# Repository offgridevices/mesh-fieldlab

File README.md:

# mesh-fieldlab

Open measurement and packet-logging tooling for LoRa mesh field tests.

**Status:** early. Structure and scope are being set up; implementation is in progress.

## Why this exists

A Meshtastic node paired with a phone shows you signal strength *live*. That is useful for a smoke test and useless for a measurement. It does not write every packet to a file, so there is no way to turn "I saw a few bars on my phone out there" into a dataset you can analyse, plot, or hand to somebody else.

`mesh-fieldlab` is the logging layer that closes that gap. It tethers to LoRa mesh nodes in the field, records what actually arrives, and writes it to disk in a stable format so that outdoor tests produce evidence instead of impressions.

## Scope

This repository is **measurement and analysis only**. Concretely, that means:

**In scope**
- Connecting to Meshtastic nodes over USB/serial (and BLE where practical)
- Recording every received packet: timestamp, source, destination, RSSI, SNR, hop count, port/type
- Stable CSV schemas that stay readable years from now
- Per-node test metadata: GPS position, antenna, height above ground, firmware and radio settings
- Derived measures such as packet delivery ratio and per-link statistics
- Analysis notebooks and plots over collected runs
- Hardware setup, wiring, and power notes for the logging rig
- Clock synchronisation and calibration procedures

**Out of scope**
- Anything unrelated to capturing or analysing measurements
- Vendored third-party source (see below)
- Credentials, API keys, or private configuration
- Raw logs containing precise coordinates of private property

## Intended hardware

- **Nodes:** RAK WisBlock / RAK4631 running Meshtastic, US915 region. Every node in a run is pinned to the **same** firmware version — currently `v2.7.26`, the `rak4631` build — because mixed versions produce measurements that look comparable and are not
- **Logger:** Seeed XIAO ESP32-C6 wired to the node's UART header, writing to a microSD card. It speaks the Meshtastic client protocol over serial — the same one a phone uses — so the node needs no modified firmware.
- **Status display:** a small OLED runs a self-test at power-up — card writable, radio answering, region and preset correct, position and clock set, which neighbours are audible — then blanks. A button wakes it for ten seconds. This is what replaces having a phone at each node.
- **Power:** a single LiPo on the node's battery connector feeds both boards; there is no second supply and no 5 V rail. A switch in the battery lead turns the whole node on and off; each power-up starts a new log file, so cycling a node is safe.
- Anything else that speaks the Meshtastic serial protocol should work.

See [docs/packet-logger-design.md](docs/packet-logger-design.md) for the wiring, file format, and validation procedure.

## Dependencies and licensing

This project depends on the official [Meshtastic Python library](https://github.com/meshtastic/Meshtastic-python) and, for the logger firmware, on [Meshtastic-arduino](https://github.com/meshtastic/Meshtastic-arduino). Both are licensed **GPL-3.0**, so **this repository is also licensed GPL-3.0**. That is a deliberate choice rather than a default: it keeps the licensing honest and unambiguous.

Expected dependency set:

| Dependency | Purpose | License |
|---|---|---|
| `meshtastic` | Node communication (Python tooling) | GPL-3.0 |
| `Meshtastic-arduino` | Node communication (logger firmware) | GPL-3.0 |
| `U8g2` | Status display (logger firmware) | BSD-2-Clause |
| `pyserial` | Serial transport | BSD-3-Clause |
| `pandas` | Log analysis | BSD-3-Clause |
| `matplotlib` | Plots | PSF-based |
| `pytest` | Tests (development only) | MIT |

If you add a dependency, record its license in this table in the same commit.

The log validator in `tools/` deliberately has **no runtime dependencies at all**: it needs to run on whatever laptop is in the field, against a card that was just pulled out of a node, without installing anything first.

### Our fork of Meshtastic-arduino

The firmware builds against [`offgridevices/Meshtastic-arduino`](https://github.com/offgridevices/Meshtastic-arduino), a fork of the upstream library, pinned to an exact commit.

The fork exists for one reason: upstream decodes each packet's RSSI and SNR and then discards them — none of its three callbacks pass those fields to the caller, and no setting changes that. Since RSSI and SNR are the entire measurement, the fork adds one additional callback carrying the full packet metadata, along with an example sketch and a host-side test suite that runs without a radio. Existing callbacks and return values are untouched. The change will be offered upstream once it has been validated in the field.

The fork remains GPL-3.0, and its commit history is the record of what was modified.

## Third-party source is never vendored here

Dependencies are installed from package managers, or referenced by URL and pinned commit. Source copies of external projects are **not** committed to this repository, and are not kept inside this working tree at all — local clones used for reading or reference live outside it, and `.gitignore` additionally blocks the usual paths (`reference/`, `vendor/`, `third_party/`, `external/`) so that an accidental copy cannot be staged.

This matters for a practical reason: license obligations travel with code. Keeping other projects' source physically outside this tree means the provenance of everything committed here is unambiguous, both for this repository and for any other project developed alongside it.

**When a dependency must be modified**, it is forked into its own repository and referenced here by URL and exact commit — never copied in and edited in place. What this repository commits is a reference, so provenance stays trivially answerable, and the fork's own commit history serves as the record of modification that GPL-3.0 requires. Record any such fork in the dependency table above, with its license and the reason it exists.

**If you are contributing:** do not paste code in from another project. Import it as a dependency, fork it and pin it, or write it yourself.

## Data handling

Collected logs are the point of this repository, but not all of them belong in it. Before committing a run:

- Confirm the test location is not private property whose coordinates you would rather not publish
- Strip or round coordinates where precision is not needed for the analysis
- Keep raw captures and processed results clearly separated

## License

GPL-3.0. See [LICENSE](LICENSE).

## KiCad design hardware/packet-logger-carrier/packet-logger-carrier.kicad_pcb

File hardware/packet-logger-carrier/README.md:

# Packet Logger Carrier Board — v1

A single 2-layer PCB that replaces the hand-wired 7 × 9 cm protoboard node.
Drop in the **RAK19003**, the **XIAO ESP32-C6** and the **microSD breakout**,
add a button and a power switch, and every connection in the build record is
made in copper instead of wire.

**Board: 86 × 58 mm, 2 layers, 1.6 mm FR4.**
65 solder points. 98 track segments, 8 vias, full ground plane underneath.

Opens in **KiCad 10** — the board file is saved in KiCad 10's own native
format and KiCad's DRC reports **0 errors, 0 warnings, 0 unconnected**.

---

## Brand colours — how to order it

**Colour is not in the Gerber files.** Soldermask and silkscreen colour are
options you pick in the fab's order form; the artwork is colour-blind. So
"on-brand" here means two things: choosing the right options, and designing
the artwork to suit them. Both are done.

| OffGrid token | On the board | Order setting |
|---|---|---|
| **Pitch** `#1B1813` | Soldermask | **Matte black** (JLCPCB "Matt Black", PCBWay "Matte Black") |
| **Bone** `#F1ECE0` | Silkscreen | **White** |
| **Ember** `#FF6A00` | The Beacon Ring, in bare metal | **ENIG** surface finish |

### The lockup

The mark and wordmark are placed at the ratios in
`handoff/logo/svg/offgrid-wordmark-horizontal.svg` — mark at `translate(20 12)`,
text anchored at `x=240 y=125`, size 92, letter-spacing −3 — scaled as one unit
so the spacing is the brand's, not an approximation. The wordmark is set in
**real Archivo weight 900 outlines**, pulled from the variable font and emitted
as filled polygons, rather than a stand-in stroke font. `src/verify_wordmark.py`
re-renders the same text through FreeType and compares shapes as a build gate.

Mark height 5.4 mm, lockup 21 mm wide, cap height 2.3 mm.

One deliberate departure: the brand SVG's own text baseline (`y=125`) leaves the
wordmark sitting about **12% of the mark height too high**, which reads as
misaligned at this size. The wordmark is dropped so its ink centre lands on the
mark's area centroid (ring + node) — the optical centre. Worth correcting in the
source asset too.

No board house offers orange soldermask, so Ember is expressed the only way a
PCB can: as **exposed copper**. The Beacon Ring is drawn on the copper layer
with a matching opening in the soldermask, so it comes out as bare gold metal
against the black — the same warm accent, in the only material the process
allows. The wordmark beside it stays white silkscreen, which keeps to the
brand's **one accent per surface** rule: the ring is the accent, everything
else is Bone on Pitch.

ENIG rather than HASL matters here — HASL would coat the mark in solder and it
would come out silver. ENIG also has a longer shelf life and a flatter finish.
It costs a little more than the default; it is the difference between a gold
mark and a grey one.

The board outline is a plain rectangle with square corners, per the brand's
right-angles-only geometry rule.

**Full order settings:** 2 layers · 1.6 mm · **Matte black** mask · **White**
silkscreen · **ENIG** finish · 86 × 58 mm · qty 5.

One practical note: matte black shows fingerprints and dust more than green,
and cosmetic consistency between batches is slightly looser. Nothing about it
affects how the board works — our traces are 0.25 mm against a 0.127 mm
process minimum, so there is a wide margin.

---

## ⚠ Read this before you order

**The RAK19003's two headers are NOT a whole number of protoboard holes apart.**

Measured from RAK's own mechanical drawings (both the Rev B dimensioned drawing
and the Rev E drawing, which agree to 0.03 mm):

| | |
|---|---|
| Pitch inside each 4-pin group | 2.54 mm |
| **Gap, J6 pin 4 (SDA) → J7 pin 1 (BOOT)** | **9.41 mm** |
| Which is | 3.70 × 2.54 — *not* 4 holes (10.16 mm) |
| Total span, pin 1 to pin 8 | 24.65 mm |

That is why the RAK was a squeeze on the protoboard: putting J6 in columns
A–D and J7 in H–K forces the pins about 0.75 mm out of place.

**How this board handles it:** J6's four pads are round holes on an exact
2.54 mm pitch. J7's four pads are **oval slots (1.0 × 2.0 mm)** centred at a
9.79 mm gap. That accepts anything from **9.24 mm to 10.34 mm**, so the board
solders up whether the true gap is the datasheet's 9.41 or a full 10.16.

**Still do this before ordering:** put a caliper across your actual RAK from
the centre of the SDA pin to the centre of the BOOT pin. Anything in
9.2 – 10.3 mm is covered.

---

## How each module sits

Hold the board with the text the right way up. Then:

**RAK19003** — pins along the bottom, body reaching up. Its USB-C, battery,
solar and reset are all on the **far (top) edge**, so they stay reachable.
Left to right the pins read:

```
J6:  VDD   GND   SCL   SDA        [ 9.41 mm gap ]        J7:  BOOT  GND  TX0  RX0
```

Confirmed two independent ways: it is what you read off your own board, and it
is what RAK's Figure 3 shows once you rotate the board 90° to match how you
have it mounted. The Rev E silkscreen says **TX0 / RX0** (the older datasheet
table calls the same pins TX1 / RX1 — same physical pins).

**XIAO ESP32-C6** — **USB-C points east**, out to the right-hand edge, so you
can plug in to reprogram it without taking anything apart. Reading the bottom
row from the USB end back: 5V, GND, 3V3, D10, D9, D8, D7 — the standard XIAO
order.

**microSD** — pins along the **top** of the module, body hanging **down toward
the bottom edge of the board**, so the card slot ends up at the edge and you
can pull the card without opening the box. Left to right the pins read:

```
3V3   CS   MOSI   CLK   MISO   GND
```

with **3V3 on the square pad** — matching the module you have.

---

## What's on the board

| Ref | What | Pins |
|---|---|---|
| J1 / J2 | RAK19003 J6 and J7 | 4 + 4 |
| J3 | XIAO ESP32-C6, 2×7, rows 15.24 mm apart | 14 |
| J4 | microSD breakout, 1×6 | 6 |
| **J5** | **OLED display — GND, 3V3, SCL, SDA. Nothing else on it.** | **4** |
| J15 | External button, if you want one off-board — BTN, GND | 2 |
| SW1 | User button, 6 mm tact, on the board | 4 |
| SW2 | **SS-12D00 / SS12D00G6 power slide switch, mounts on the board** | 3 |
| J12 / J13 | Battery in — bare wires or JST-PH 2.0, wired in parallel | 2 + 2 |
| J14 | Switched battery out → the RAK's own battery socket | 2 |
| J10 | RAK spare: BOOT, SCL, SDA, GND | 4 |
| J11 | ESP spare: 5V, D1, D2, GND | 4 |
| JP1 | 3V3 link — **fit a shunt** (see below) | 2 |
| C1–C4 | Decoupling, all optional, all 2.54 mm lead pitch | 8 |

### The power switch

**SW2 takes your SS12D00G6 directly** — three pins on 2.54 mm, which is
exactly what that switch has, so it drops in and solders. The body outline on
the silkscreen is the 8.0 × 4.0 mm footprint of the switch. The **centre pin
is the input** (battery +); the switched output leaves on the pin marked OUT.
The third pin is unconnected. If you would rather use a panel switch, wire it
to OUT and IN instead.

### The display

**J5 is the display and only the display** — four pins, GND, 3V3, SCL, SDA,
all together, labelled on the board. The button is a separate 2-pin header
(J15) right next to it, wired in parallel with the button on the board, so you
can use either, both, or neither.

### The 3V3 link (JP1)

The RAK's 3.3 V comes in on JP1's "RAK" pin and leaves on "SYS" to feed the
XIAO, the card and the OLED. Fit a jumper shunt for normal use.

Pull the shunt when you want to program the XIAO over USB with the RAK
powered — it stops the RAK's regulator and the XIAO's regulator fighting over
the same rail. With the shunt out, USB still powers the XIAO, the card and
the screen; only the RAK is separated. If you'd rather never think about it,
bridge the two pads with solder.

---

## Ordering

JLCPCB or PCBWay:

* 2 layers, 1.6 mm, **matte black mask, white silkscreen, ENIG finish** (see Brand colours above)
* **86 × 58 mm** — inside the cheap 100 × 100 mm tier
* Upload `packet-logger-carrier-gerbers.zip` as-is
* Minimum order is 5; you need 4, so you get a spare
* Expect roughly $2–5 for the bare boards; ENIG and the black mask add a
  few dollars. Plus shipping, about 1–2 weeks.

The zip contains top and bottom copper, both soldermasks, top silkscreen,
board outline, and separate plated / non-plated drill files. J7's oval slots
are in the plated drill file as routed slots (G85) — both houses handle these
as standard.

---

## Assembly order

1. **C1–C4 first** if you're fitting them (lowest parts first). They're optional.
2. **JP1**, then the shunt.
3. **SW1** the tact switch, **SW2** the slide switch.
4. **J12/J13** battery in, **J14** battery out.
5. **J5, J10, J11, J15** male headers.
6. **Female headers last**: J1, J2 (RAK), J3 (XIAO), J4 (card).
7. Plug the modules in. Wire a JST-PH pigtail from **J14** to the RAK's own
   battery socket, and a 4-way cable from **J5** to the display.

Every GND pin sits on a thermal relief, so they solder with a normal iron
instead of sinking all the heat into the ground plane.

### Mounting the modules

Every module interface is a plain 2.54 mm through-hole header, so you can
either socket the module on female headers (easy to swap, ~8.5 mm tall) or
solder wires straight into the same holes and mount the module elsewhere.
Both work.

If you solder a module down flat instead of on headers, note that signal
traces do run underneath it. They are covered by soldermask, so this is
fine — just don't scrape it.

---

## What was checked

Two independent sets of checks, plus KiCad's own:

| Check | Result |
|---|---|
| **KiCad 10 DRC** (the real thing, zones filled) | **0 errors, 0 warnings, 0 unconnected** |
| Copper clearance, every pair of objects on a shared layer | **pass** — 0.25 mm minimum |
| Net connectivity, by flood-fill over both layers | **pass** — every pad on every net reachable |
| Netlist vs. the proven protoboard wiring | **pass** — identical, pin for pin |
| Drill-to-drill spacing | **pass** — minimum 0.45 mm |
| Annular ring | **pass** — minimum 0.15 mm |
| Copper and drills inside the board edge | **pass** |
| Ground pour reaches every GND pad through its thermal spokes | **pass** — all 16 |
| Silkscreen collisions (text/text, text/pad, text/line) | **pass** — none |
| **Gerber round-trip**: emitted Gerbers re-read by a separate parser and compared to the model | **pass** — 0.0000 mm² difference on both copper layers |
| **Cross-check vs KiCad's own Gerber export** of the same board | **F.Cu 0.000 mm², Edge.Cuts 0.000 mm², masks 0.06 mm²** |
| Brand accent is on copper + mask, never silkscreen (regression gate) | **pass** — 37 items on each |
| Silkscreen over mounting holes | **pass** — none |
| Every region inspected visually at readable magnification, both sides | **done** |
| Wordmark outlines vs an independent FreeType rendering | **match** — IoU 0.94, aspect within 0.6% |

The strongest of these is the cross-check: KiCad was asked to export its own
Gerbers from the same board, and its top copper and board outline match ours
to **zero measurable difference**, logo included. The bottom copper differs by
about 1% — entirely at the pour's outer edge and around thermal spokes, where
two different pour algorithms are simply allowed to disagree. Both are valid.

`render3d_top.png` and `render3d_bottom.png` are KiCad's own 3D renders using
the board stackup, so they show the finished product in the colours it will be
built in.

`fab_top.png` and `fab_bottom.png` are rendered *from the Gerbers themselves*,
not from the design, and in the brand colours the board will actually be
ordered in - so what you see there is what will be manufactured.

---

## Assumptions worth knowing

1. **microSD module size.** The six pads and their order are certain (you read
   them off the board). I reserved a 24 × 21 mm box for the body, shown dashed
   on the silkscreen, with the card slot pointing at the board edge. If your
   module is longer it will simply overhang the edge, which is fine — better,
   even. If it is much shorter, the slot will sit a few mm inside the edge and
   the enclosure cut-out needs to allow for that.
2. **OLED pin order** is taken as GND, 3V3, SCL, SDA, the usual order on a
   0.91" I2C module and the same order as your existing lid cable. Worth a
   glance at your screen before you solder the header.
3. **XIAO row spacing** is 15.24 mm (0.6"), the standard for every XIAO. This
   matches your protoboard, where the two columns were six holes apart.
4. **The RAK gap**, as above — the one thing to measure.
5. There is no schematic file, only the PCB. `netlist.csv` is the full record
   of what connects to what.

## Files

```
packet-logger-carrier.kicad_pcb      open this in KiCad 10
packet-logger-carrier.kicad_pro      project file
packetlogger.pretty/                 footprint library (so nothing is unresolved)
fp-lib-table                         points KiCad at that library
packet-logger-carrier-gerbers.zip    <- upload this to JLCPCB / PCBWay
gerbers/                             the same files, unzipped
netlist.csv                          every pad, its net and its position
bom.csv                              what to buy
kicad-drc.json                       KiCad's own DRC report
fab_top.png / fab_bottom.png         rendered from the Gerbers
render3d_top.png / render3d_bottom.png   KiCad's 3D render, real colours
board.png                            routing view (top = red, bottom = blue)
mechanical/                          STEP models + sizes for enclosure design
src/                                 the generator and every verification script
```

For an enclosure, start at `mechanical/README.md`. It has the STEP files, the
overall envelope, the M3 pattern and which face each connector needs an
opening on.

To open: `File → Open`, pick `packet-logger-carrier.kicad_pcb`. The ground
pour is already filled, so it looks right immediately.

To rebuild everything from source: `cd src && python make.py` — it routes,
runs every check, writes the KiCad and Gerber files, hands the board to
KiCad 10 for a final DRC, and refuses to finish if anything fails.

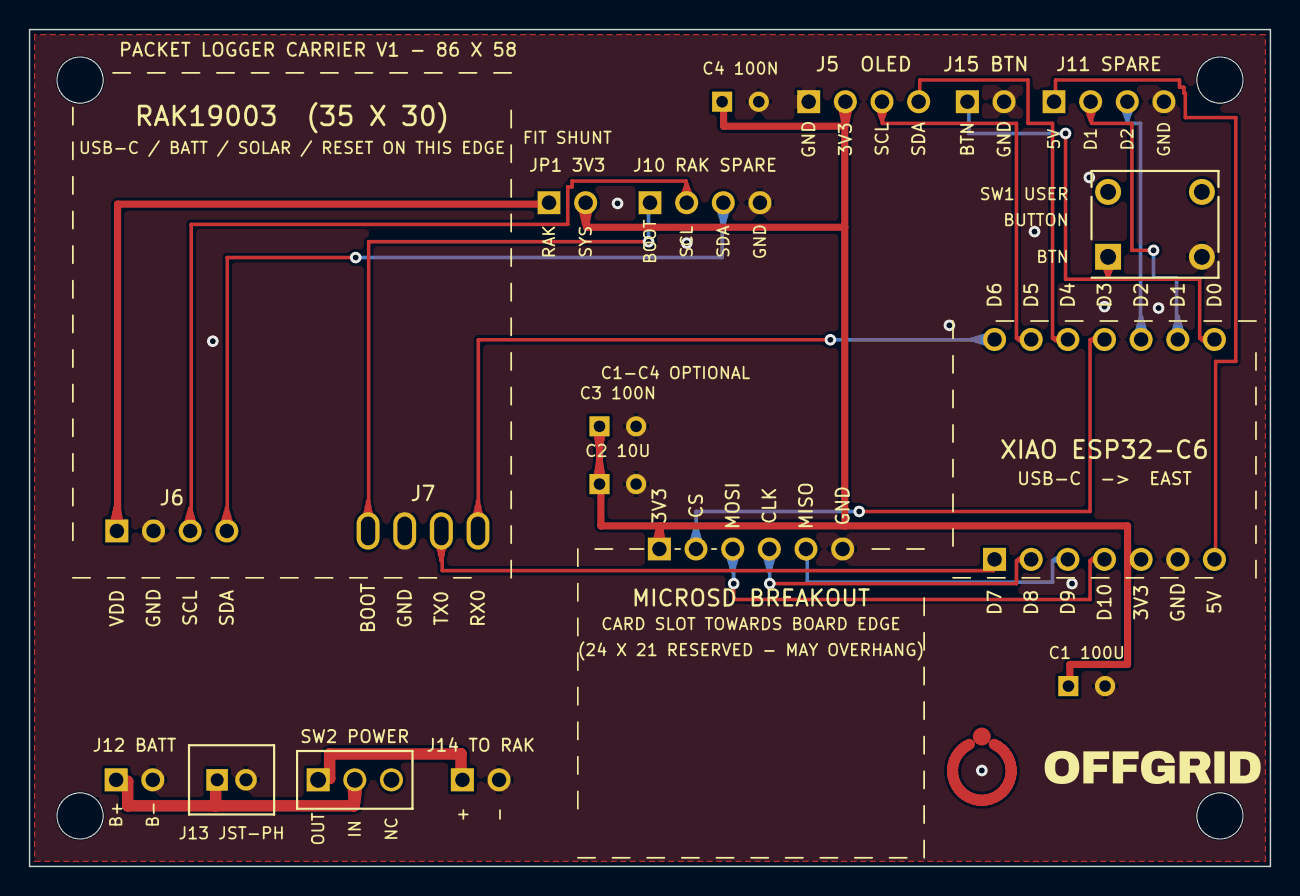
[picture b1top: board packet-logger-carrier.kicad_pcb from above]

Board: 2 copper layers, 86.0 x 58.0 mm, 22 parts (0 on the bottom side), 20 nets.

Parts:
C1: 100u; C1
C2: 10u; C2
C3: 100n; C3
C4: 100n; C4
H1, H2, H3, H4: M3; MountingHole
J1: RAK19003 J6; J1
J2: RAK19003 J7; J2
J3: XIAO ESP32-C6; J3
J4: microSD; J4
J5: LID CABLE; J5
J10: RAK SPARE; J10
J11: ESP SPARE; J11
J12: BATT IN; J12
J13: BATT JST-PH; J13
J14: BATT TO RAK; J14
J15: J15
JP1: 3V3 LINK; JP1
SW1: USER BUTTON; SW1
SW2: POWER SWITCH; SW2

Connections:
+3V3: C1.1, C2.1, C3.1, C4.1, J3.5, J4.1, J5.2, JP1.2
BAT+: J12.1, J13.1, SW2.2
BAT_SW: J14.1, SW2.1
BTN: J3.14, J15.1, SW1.1
GND: C1.2, C2.2, C3.2, C4.2, J1.2, J2.2, J3.6, J4.6, J5.1, J10.4, J11.4, J12.2, J13.2, J14.2, J15.2, SW1.2
OLED_SCL: J3.9, J5.3
OLED_SDA: J3.10, J5.4
RAK_BOOT: J2.1, J10.1
RAK_RX0: J2.4, J3.8
RAK_SCL: J1.3, J10.2
RAK_SDA: J1.4, J10.3
RAK_TX0: J2.3, J3.1
RAW_3V3: J1.1, JP1.1
SD_CLK: J3.2, J4.4
SD_CS: J3.11, J4.2
SD_MISO: J3.3, J4.5
SD_MOSI: J3.4, J4.3
XIAO_5V: J3.7, J11.1
XIAO_D1: J3.13, J11.2
XIAO_D2: J3.12, J11.3
